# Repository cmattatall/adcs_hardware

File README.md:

# adcs_hardware
Hardware repository for ADCS

# Harware Architecture Overview

# VERSION CONTROL

WHENEVER A SHEMATIC REVISION IS COMPLETED, UNLIKE SOFTWARE, BRANCHES SHOULD NOT BE MERGED. THEY SHOULD BE FROZEN.

TO START A REVISION, THE CURRENT "HEAD" SHOULD BE FORKED (READ: MAKE A NEW BRANCH) NAMED APPROPRIATELY. 

If the revision is accepted and the design changes pass review, the revision branch then becomes the new master branch.

This way, the last "stable" revision branch (the old master branch) remains completely unchanged and unaffected by deltas made in the forked branch.

If there is ever an issue, the old version can be selected SIMPLY by switching back to the old branch, no merging should ever occur.

# Cloning repo for use in Eagle

Clone Repo into your local eagle projects repository
ie: C:/Users/user/Documents/Eagle/projects/

Repo will then appear under projects tab of the 'Control Panel' window when Eagle is launched.

# Eagle File Types Notes
 
## Project Manager File
*.epf is the eagle project manager file and contains all settings information for project. Contains all path references to all the libraries the have been used. *.epf is not crucial to project but can be useful to share with collaborators. 

## Design Files 
*.brd and *.sch files must have matching names and be contained in the same folder. Schematic files also copy all the information from the component libraries once the components are placed in a schematic, making the library files less necessary once used. The .brd files also copy the package information from the component libraries and don’t require libraries again unless you need to place a new component or replace a previous component. 

## Backup Files
*.b#x and *.s#x files are local backups by Eagle. By default Eagle saves 9 backups (9 is also the max).

## Libraries
Libraries are the templates for components. They are unique files that all the information on a specific component that Eagle CAD requires for design. They are the building blocks that contain information like pin numbers, terminal names, symbol shape, package type and footprint size etc. A library has both a symbol (used in schematics) and a package (footprint for pcb layout). Once a library is used in an Eagle design, it is no longer required as Eagle copies all the information over to the schematic and board files. However, while working with your team, it is recommended to share and use the same libraries to keep your designs consistent.

Custom library parts have been saved in managed library: https://library.io/libraries/22876504-my_library

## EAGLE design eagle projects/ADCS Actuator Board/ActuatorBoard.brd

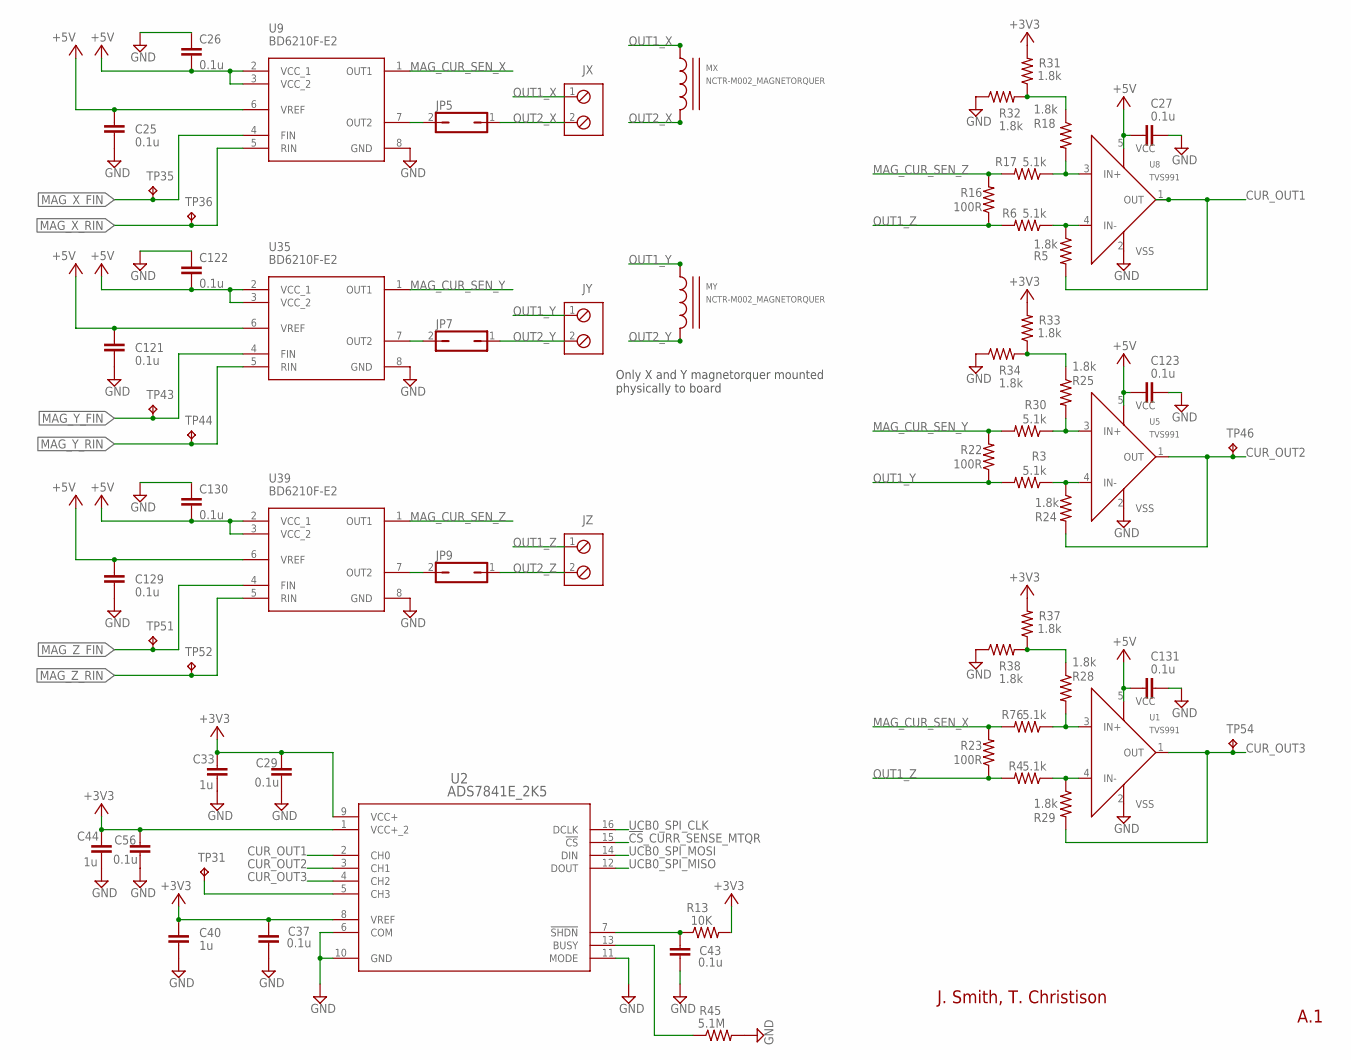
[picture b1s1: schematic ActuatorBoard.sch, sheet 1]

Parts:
C25, C26, C121, C122, C129, C130: 0.1u; C0603
C27, C29, C37, C43, C56, C123, C131: 0.1u; C0402
C33, C40, C44: 1u; C0402
JP5, JP7, JP9: JP1Q_; 1X02
JX: TRM_BLK_1X2; 2POL254
JY: TRM_BLK_1X2; 2POL254
JZ: TRM_BLK_1X2; 2POL254
MX: NCTR-M002_MAGNETORQUER; MAG_MOUNT_V3
MY: NCTR-M002_MAGNETORQUER; MAG_MOUNT_V3
R3, R4, R6, R17, R30, R76: 5.1k; R0402
R5, R18, R24, R25, R28, R29, R31, R32, R33, R34, R37, R38: 1.8k; R0402
R13: 10K; R0402
R16, R22, R23: 100R; M0805
R45: 5.1M; R0402
TP31, TP35, TP36, TP43, TP44, TP46, TP51, TP52, TP54: TESTPOINT; TP_P76H50
U1, U5, U8: TVS991; SOT95P280X145-5N
U2: ADS7841E_2K5; DBQ16
U9, U35, U39: BD6210F-E2; BD6221F-E2_SOIC8P127_500X620X171L30X42N

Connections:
!CS!_CURR_SENSE_MTQR: U2.15 (!CS); also elsewhere on the board
+3V3: C29.1, C33.1, C37.1, C40.1, C44.1, C56.1, R13.2, R31.2, R33.2, R37.2, U2.1 (VCC+_2), U2.8 (VREF), U2.9 (VCC+); also elsewhere on the board
+5V: C25.1, C26.2, C27.1, C121.1, C122.2, C123.1, C129.1, C130.2, C131.1, U1.5 (VCC), U5.5 (VCC), U8.5 (VCC), U9.2 (VCC_1), U9.3 (VCC_2), U9.6 (VREF), U35.2 (VCC_1), U35.3 (VCC_2), U35.6 (VREF), U39.2 (VCC_1), U39.3 (VCC_2), U39.6 (VREF); also elsewhere on the board
CUR_OUT1: R5.2, U2.2 (CH0), U8.1 (OUT)
CUR_OUT2: R24.2, TP46.1, U2.3 (CH1), U5.1 (OUT)
CUR_OUT3: R29.2, TP54.1, U1.1 (OUT), U2.4 (CH2)
GND: C25.2, C26.1, C27.2, C29.2, C33.2, C37.2, C40.2, C43.2, C44.2, C56.2, C121.2, C122.1, C123.2, C129.2, C130.1, C131.2, R32.1, R34.1, R38.1, R45.2, U1.2 (VSS), U2.6 (COM), U2.10 (GND), U2.11 (MODE), U5.2 (VSS), U8.2 (VSS), U9.8 (GND), U35.8 (GND), U39.8 (GND); also elsewhere on the board
MAG_CUR_SEN_X: R23.2, R76.2, U9.1 (OUT1)
MAG_CUR_SEN_Y: R22.2, R30.2, U35.1 (OUT1)
MAG_CUR_SEN_Z: R16.2, R17.2, U39.1 (OUT1)
MAG_X_FIN: TP35.1, U9.4 (FIN); also elsewhere on the board
MAG_X_RIN: TP36.1, U9.5 (RIN); also elsewhere on the board
MAG_Y_FIN: TP43.1, U35.4 (FIN)
MAG_Y_RIN: TP44.1, U35.5 (RIN); also elsewhere on the board
MAG_Z_FIN: TP51.1, U39.4 (FIN); also elsewhere on the board
MAG_Z_RIN: TP52.1, U39.5 (RIN); also elsewhere on the board
unnamed: R45.1, U2.13 (BUSY)
unnamed: R5.1, R6.1, U8.4 (IN-)
unnamed: R3.1, R24.1, U5.4 (IN-)
unnamed: R4.1, R29.1, U1.4 (IN-)
unnamed: R17.1, R18.2, U8.3 (IN+)
unnamed: R25.2, R30.1, U5.3 (IN+)
unnamed: R28.2, R76.1, U1.3 (IN+)
unnamed: C43.1, R13.1, U2.7 (!SHDN)
unnamed: TP31.1, U2.5 (CH3)
unnamed: JP5.2, U9.7 (OUT2)
unnamed: R33.1, R34.2
unnamed: R28.1, R37.1, R38.2
unnamed: R18.1, R31.1, R32.2
unnamed: JP7.2, U35.7 (OUT2)
unnamed: JP9.2, U39.7 (OUT2)
OUT1_X: JX.1
OUT1_Y: JY.1, R3.2, R22.1
OUT1_Z: JZ.1, R4.2, R6.2, R16.1, R23.1
OUT2_X: JP5.1, JX.2
OUT2_Y: JP7.1, JY.2
OUT2_Z: JP9.1, JZ.2
UCB0_SPI_CLK: U2.16 (DCLK); also elsewhere on the board
UCB0_SPI_MISO: U2.12 (DOUT); also elsewhere on the board
UCB0_SPI_MOSI: U2.14 (DIN); also elsewhere on the board

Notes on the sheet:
A.1
Only X and Y magnetorquer mounted physically to board
J. Smith, T. Christison

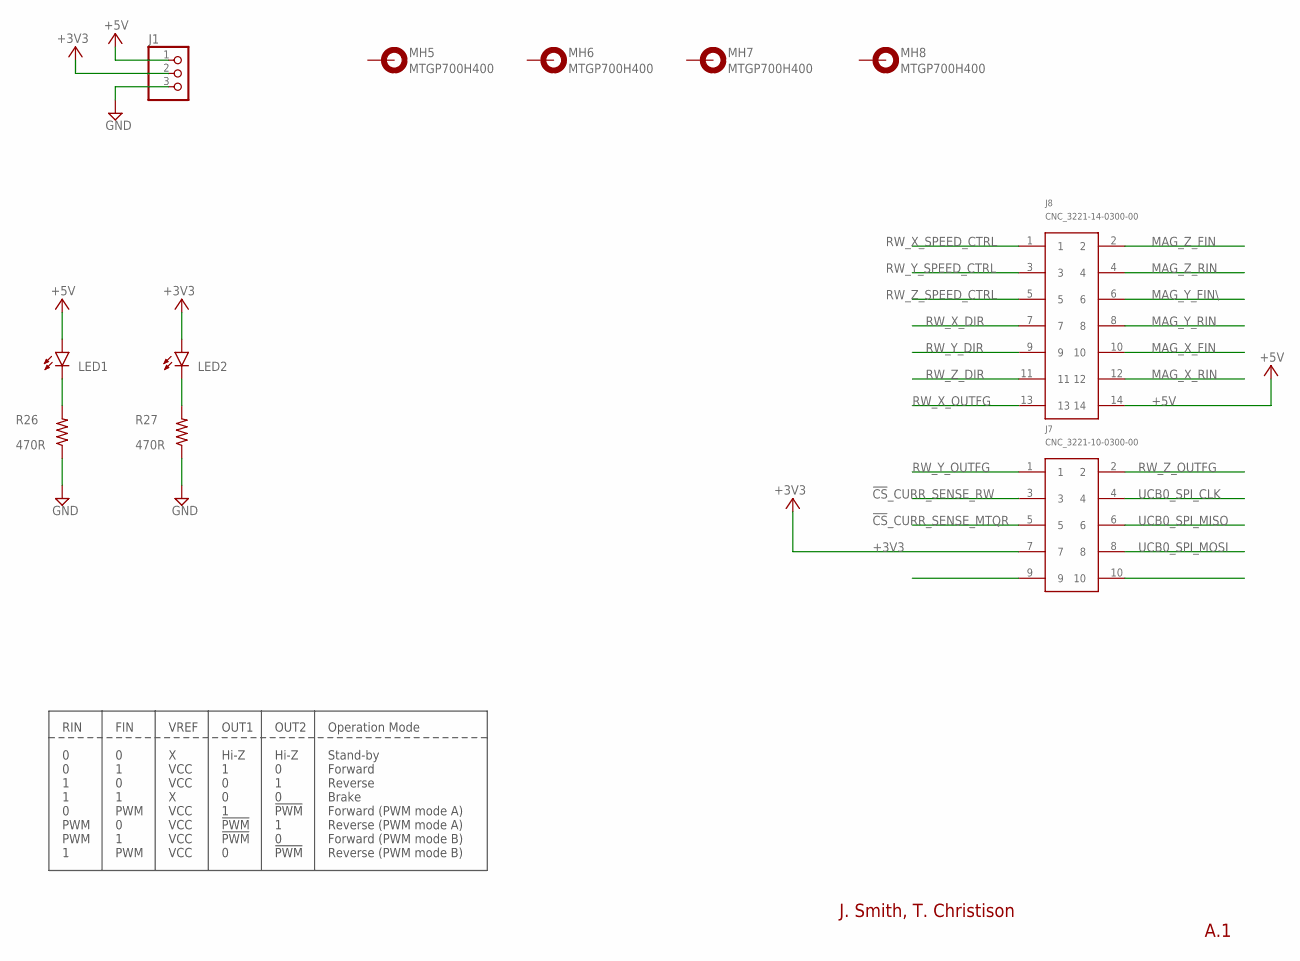
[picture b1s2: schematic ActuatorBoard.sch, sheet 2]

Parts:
J1: PINHD-1X3; 1X03
J7: CNC_3221-10-0300-00
J8: CNC_3221-14-0300-00
LED1, LED2: LEDCHIPLED_0603; CHIPLED_0603
MH5, MH6, MH7, MH8: MTGP700H400
R26, R27: 470R; R0603

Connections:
!CS!_CURR_SENSE_MTQR: J7.5; also elsewhere on the board
!CS!_CURR_SENSE_RW: J7.3; also elsewhere on the board
+3V3: J1.2, J7.7, LED2.A; also elsewhere on the board
+5V: J1.1, J8.14, LED1.A; also elsewhere on the board
GND: J1.3, R26.1, R27.1; also elsewhere on the board
MAG_X_FIN: J8.10; also elsewhere on the board
MAG_X_RIN: J8.12; also elsewhere on the board
MAG_Y_FIN\: J8.6
MAG_Y_RIN: J8.8; also elsewhere on the board
MAG_Z_FIN: J8.2; also elsewhere on the board
MAG_Z_RIN: J8.4; also elsewhere on the board
unnamed: LED1.C, R26.2
unnamed: LED2.C, R27.2
RW_X_DIR: J8.7; also elsewhere on the board
RW_X_OUTFG: J8.13; also elsewhere on the board
RW_X_SPEED_CTRL: J8.1; also elsewhere on the board
RW_Y_DIR: J8.9; also elsewhere on the board
RW_Y_OUTFG: J7.1; also elsewhere on the board
RW_Y_SPEED_CTRL: J8.3; also elsewhere on the board
RW_Z_DIR: J8.11; also elsewhere on the board
RW_Z_OUTFG: J7.2; also elsewhere on the board
RW_Z_SPEED_CTRL: J8.5; also elsewhere on the board
UCB0_SPI_CLK: J7.4; also elsewhere on the board
UCB0_SPI_MISO: J7.6; also elsewhere on the board
UCB0_SPI_MOSI: J7.8; also elsewhere on the board

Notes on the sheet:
A.1
FIN 0 1 0 1 PWM 0 1 PWM
RIN 0 0 1 1 0 PWM PWM 1
VREF X VCC VCC X VCC VCC VCC VCC
OUT1 Hi-Z 1 0 0 1 !PWM !PWM 0
OUT2 Hi-Z 0 1 0 !PWM 1 0 !PWM
Operation Mode Stand-by Forward Reverse Brake Forward (PWM mode A) Reverse (PWM mode A) Forward (PWM mode B) Reverse (PWM mode B)
J. Smith, T. Christison

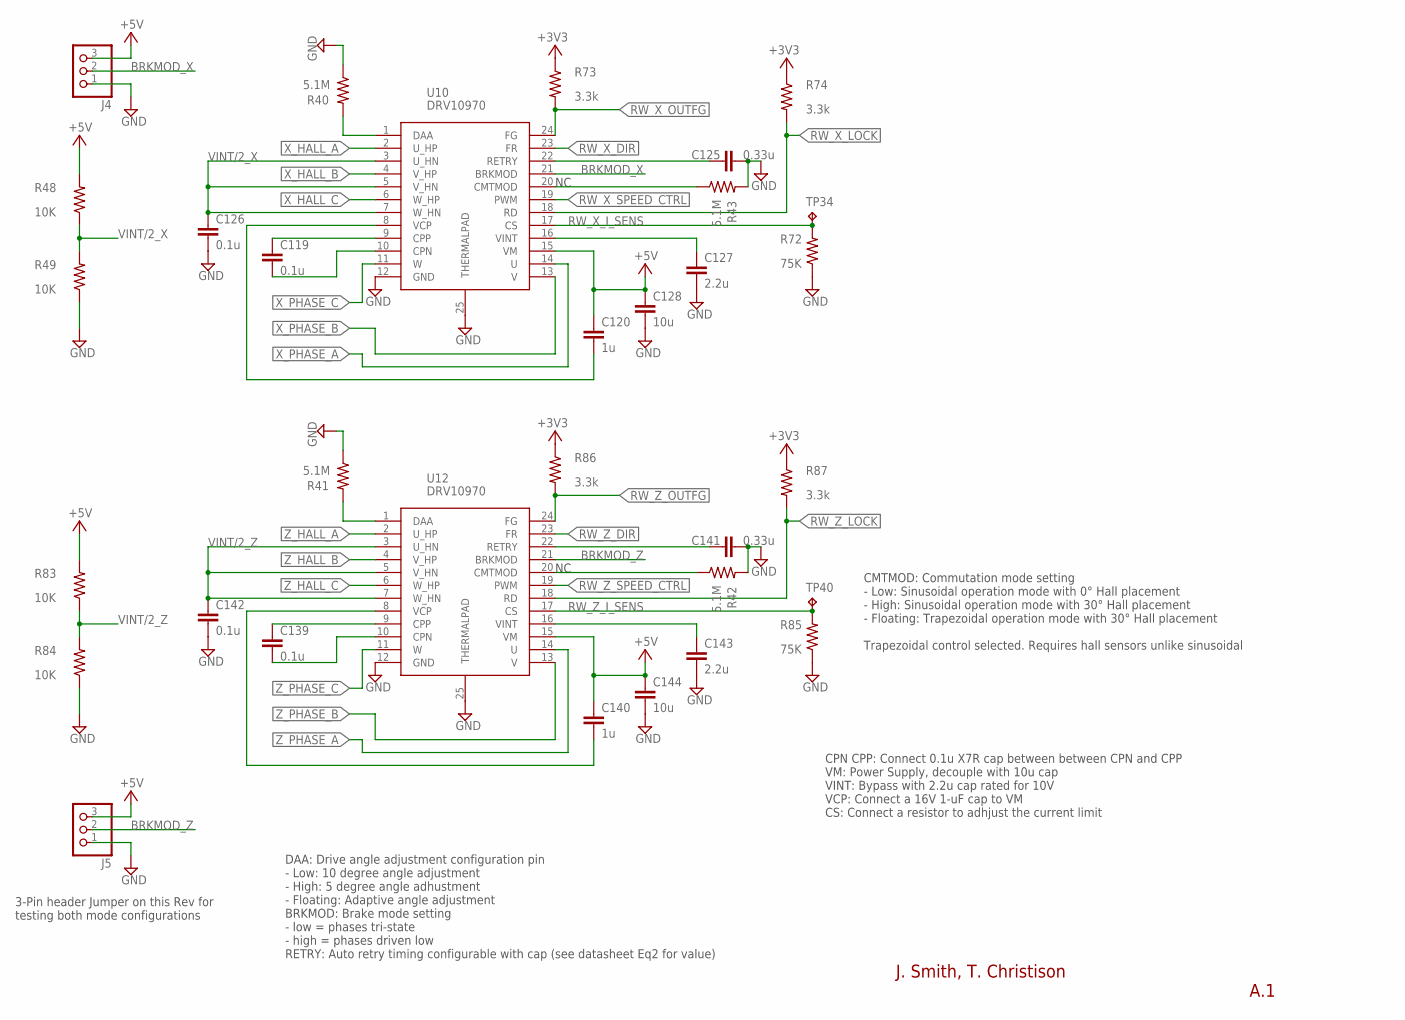
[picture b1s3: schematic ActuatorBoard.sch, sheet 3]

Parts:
C119, C126, C139, C142: 0.1u; C0603
C120, C140: 1u; C0603
C125, C141: 0.33u; C0603
C127, C143: 2.2u; C0603
C128, C144: 10u; C0603
J4, J5: PINHD-1X3; 1X03
R40, R41, R42, R43: 5.1M; R0402
R48, R49, R83, R84: 10K; R0603
R72, R85: 75K; R0603
R73, R74, R86, R87: 3.3k; R0603
TP34, TP40: TESTPOINT; TP_P76H50
U10, U12: DRV10970_MOTOR_DRIVERDRV10970; SOP65P640X120-25T240X328N

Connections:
+3V3: R73.1, R74.1, R86.1, R87.1; also elsewhere on the board
+5V: C120.1, C128.1, C140.1, C144.1, J4.3, J5.3, R48.2, R83.2, U10.15 (VM), U12.15 (VM); also elsewhere on the board
BRKMOD_X: J4.2, U10.21 (BRKMOD)
BRKMOD_Z: J5.2, U12.21 (BRKMOD)
GND: C125.2, C126.2, C127.2, C128.2, C141.2, C142.2, C143.2, C144.2, J4.1, J5.1, R40.1, R41.1, R42.2, R43.2, R49.1, R72.1, R84.1, R85.1, U10.12 (GND), U10.25 (THERMALPAD), U12.12 (GND), U12.25 (THERMALPAD); also elsewhere on the board
unnamed: R40.2, U10.1 (DAA)
unnamed: R41.2, U12.1 (DAA)
unnamed: R42.1, U12.20 (CMTMOD)
unnamed: R43.1, U10.20 (CMTMOD)
unnamed: C119.1, U10.9 (CPP)
unnamed: C120.2, U10.8 (VCP)
unnamed: C119.2, U10.10 (CPN)
unnamed: C127.1, U10.16 (VINT)
unnamed: C125.1, U10.22 (RETRY)
unnamed: C139.1, U12.9 (CPP)
unnamed: C140.2, U12.8 (VCP)
unnamed: C139.2, U12.10 (CPN)
unnamed: C143.1, U12.16 (VINT)
unnamed: C141.1, U12.22 (RETRY)
RW_X_DIR: U10.23 (FR); also elsewhere on the board
RW_X_I_SENS: R72.2, TP34.1, U10.17 (CS); also elsewhere on the board
RW_X_LOCK: R74.2, U10.18 (RD)
RW_X_OUTFG: R73.2, U10.24 (FG); also elsewhere on the board
RW_X_SPEED_CTRL: U10.19 (PWM); also elsewhere on the board
RW_Z_DIR: U12.23 (FR); also elsewhere on the board
RW_Z_I_SENS: R85.2, TP40.1, U12.17 (CS); also elsewhere on the board
RW_Z_LOCK: R87.2, U12.18 (RD)
RW_Z_OUTFG: R86.2, U12.24 (FG); also elsewhere on the board
RW_Z_SPEED_CTRL: U12.19 (PWM); also elsewhere on the board
VINT/2_X: C126.1, R48.1, R49.2, U10.3 (U_HN), U10.5 (V_HN), U10.7 (W_HN)
VINT/2_Z: C142.1, R83.1, R84.2, U12.3 (U_HN), U12.5 (V_HN), U12.7 (W_HN)
X_HALL_A: U10.2 (U_HP); also elsewhere on the board
X_HALL_B: U10.4 (V_HP); also elsewhere on the board
X_HALL_C: U10.6 (W_HP); also elsewhere on the board
X_PHASE_A: U10.14 (U); also elsewhere on the board
X_PHASE_B: U10.13 (V); also elsewhere on the board
X_PHASE_C: U10.11 (W); also elsewhere on the board
Z_HALL_A: U12.2 (U_HP); also elsewhere on the board
Z_HALL_B: U12.4 (V_HP); also elsewhere on the board
Z_HALL_C: U12.6 (W_HP); also elsewhere on the board
Z_PHASE_A: U12.14 (U); also elsewhere on the board
Z_PHASE_B: U12.13 (V); also elsewhere on the board
Z_PHASE_C: U12.11 (W); also elsewhere on the board

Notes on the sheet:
CPN CPP: Connect 0.1u X7R cap between between CPN and CPP VM: Power Supply, decouple with 10u cap VINT: Bypass with 2.2u cap rated for 10V VCP: Connect a 16V 1-uF cap to VM CS: Connect a resistor to adhjust the current limit
DAA: Drive angle adjustment configuration pin - Low: 10 degree angle adjustment - High: 5 degree angle adhustment - Floating: Adaptive angle adjustment BRKMOD: Brake mode setting - low = phases tri-state - high = phases driven low RETRY: Auto retry timing configurable with cap (see datasheet Eq2 fo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
CMTMOD: Commutation mode setting - Low: Sinusoidal operation mode with 0° Hall placement - High: Sinusoidal operation mode with 30° Hall placement - Floating: Trapezoidal operation mode with 30° Hall placement Trapezoidal control selected. Requires hall sensors unlike sinusoidal
A.1
3-Pin header Jumper on this Rev for testing both mode configurations
J. Smith, T. Christison

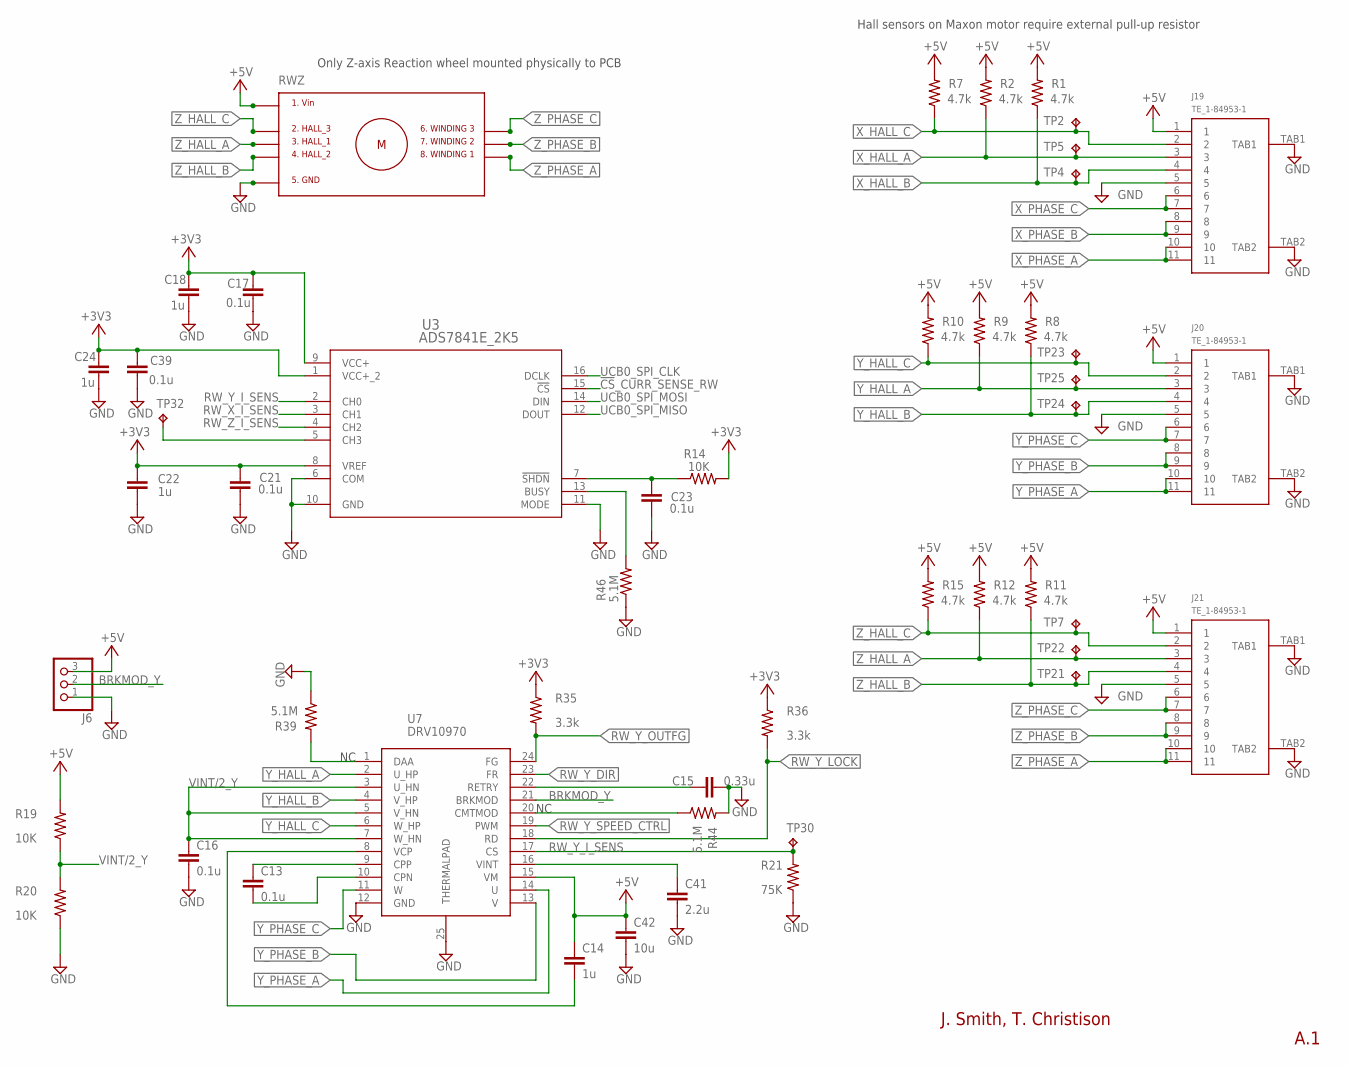
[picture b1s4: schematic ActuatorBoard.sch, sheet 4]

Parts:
C13, C16: 0.1u; C0603
C14: 1u; C0603
C15: 0.33u; C0603
C17, C21, C23, C39: 0.1u; C0402
C18, C22, C24: 1u; C0402
C41: 2.2u; C0603
C42: 10u; C0603
J6: PINHD-1X3; 1X03
J19, J20, J21: TE_1-84953-1
R1, R2, R7, R8, R9, R10, R11, R12, R15: 4.7k; R0402
R14: 10K; R0402
R19, R20: 10K; R0603
R21: 75K; R0603
R35, R36: 3.3k; R0603
R39, R44, R46: 5.1M; R0402
RWZ: REACTION_WHEEL_NOPINS_MAXON; RWA_NOPINS
TP2, TP4, TP5, TP7, TP21, TP22, TP23, TP24, TP25, TP30, TP32: TESTPOINT; TP_P76H50
U3: ADS7841E_2K5; DBQ16
U7: DRV10970_MOTOR_DRIVERDRV10970; SOP65P640X120-25T240X328N

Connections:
!CS!_CURR_SENSE_RW: U3.15 (!CS); also elsewhere on the board
+3V3: C17.1, C18.1, C21.1, C22.1, C24.1, C39.1, R14.2, R35.1, R36.1, U3.1 (VCC+_2), U3.8 (VREF), U3.9 (VCC+); also elsewhere on the board
+5V: C14.1, C42.1, J6.3, J19.1, J20.1, J21.1, R1.2, R2.2, R7.2, R8.2, R9.2, R10.2, R11.2, R12.2, R15.2, R19.2, U7.15 (VM); also elsewhere on the board
BRKMOD_Y: J6.2, U7.21 (BRKMOD)
GND: C15.2, C16.2, C17.2, C18.2, C21.2, C22.2, C23.2, C24.2, C39.2, C41.2, C42.2, J6.1, J19.5, J19.TAB1, J19.TAB2, J20.5, J20.TAB1, J20.TAB2, J21.5, J21.TAB1, J21.TAB2, R20.1, R21.1, R39.1, R44.2, R46.1, U3.6 (COM), U3.10 (GND), U3.11 (MODE), U7.12 (GND), U7.25 (THERMALPAD); also elsewhere on the board
unnamed: R46.2, U3.13 (BUSY)
unnamed: R39.2, U7.1 (DAA)
unnamed: C23.1, R14.1, U3.7 (!SHDN)
unnamed: TP32.1, U3.5 (CH3)
unnamed: R44.1, U7.20 (CMTMOD)
unnamed: C13.1, U7.9 (CPP)
unnamed: C14.2, U7.8 (VCP)
unnamed: C13.2, U7.10 (CPN)
unnamed: C41.1, U7.16 (VINT)
unnamed: C15.1, U7.22 (RETRY)
RW_X_I_SENS: U3.3 (CH1); also elsewhere on the board
RW_Y_DIR: U7.23 (FR); also elsewhere on the board
RW_Y_I_SENS: R21.2, TP30.1, U3.2 (CH0), U7.17 (CS)
RW_Y_LOCK: R36.2, U7.18 (RD)
RW_Y_OUTFG: R35.2, U7.24 (FG); also elsewhere on the board
RW_Y_SPEED_CTRL: U7.19 (PWM); also elsewhere on the board
RW_Z_I_SENS: U3.4 (CH2); also elsewhere on the board
UCB0_SPI_CLK: U3.16 (DCLK); also elsewhere on the board
UCB0_SPI_MISO: U3.12 (DOUT); also elsewhere on the board
UCB0_SPI_MOSI: U3.14 (DIN); also elsewhere on the board
VINT/2_Y: C16.1, R19.1, R20.2, U7.3 (U_HN), U7.5 (V_HN), U7.7 (W_HN)
X_HALL_A: J19.3, R2.1, TP5.1; also elsewhere on the board
X_HALL_B: J19.4, R1.1, TP4.1; also elsewhere on the board
X_HALL_C: J19.2, R7.1, TP2.1; also elsewhere on the board
X_PHASE_A: J19.10, J19.11; also elsewhere on the board
X_PHASE_B: J19.8, J19.9; also elsewhere on the board
X_PHASE_C: J19.6, J19.7; also elsewhere on the board
Y_HALL_A: J20.3, R9.1, TP25.1, U7.2 (U_HP)
Y_HALL_B: J20.4, R8.1, TP24.1, U7.4 (V_HP)
Y_HALL_C: J20.2, R10.1, TP23.1, U7.6 (W_HP)
Y_PHASE_A: J20.10, J20.11, U7.14 (U)
Y_PHASE_B: J20.8, J20.9, U7.13 (V)
Y_PHASE_C: J20.6, J20.7, U7.11 (W)
Z_HALL_A: J21.3, R12.1, TP22.1; also elsewhere on the board
Z_HALL_B: J21.4, R11.1, TP21.1; also elsewhere on the board
Z_HALL_C: J21.2, R15.1, TP7.1; also elsewhere on the board
Z_PHASE_A: J21.10, J21.11; also elsewhere on the board
Z_PHASE_B: J21.8, J21.9; also elsewhere on the board
Z_PHASE_C: J21.6, J21.7; also elsewhere on the board

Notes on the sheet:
A.1
Hall sensors on Maxon motor require external pull-up resistor
Only Z-axis Reaction wheel mounted physically to PCB
J. Smith, T. Christison

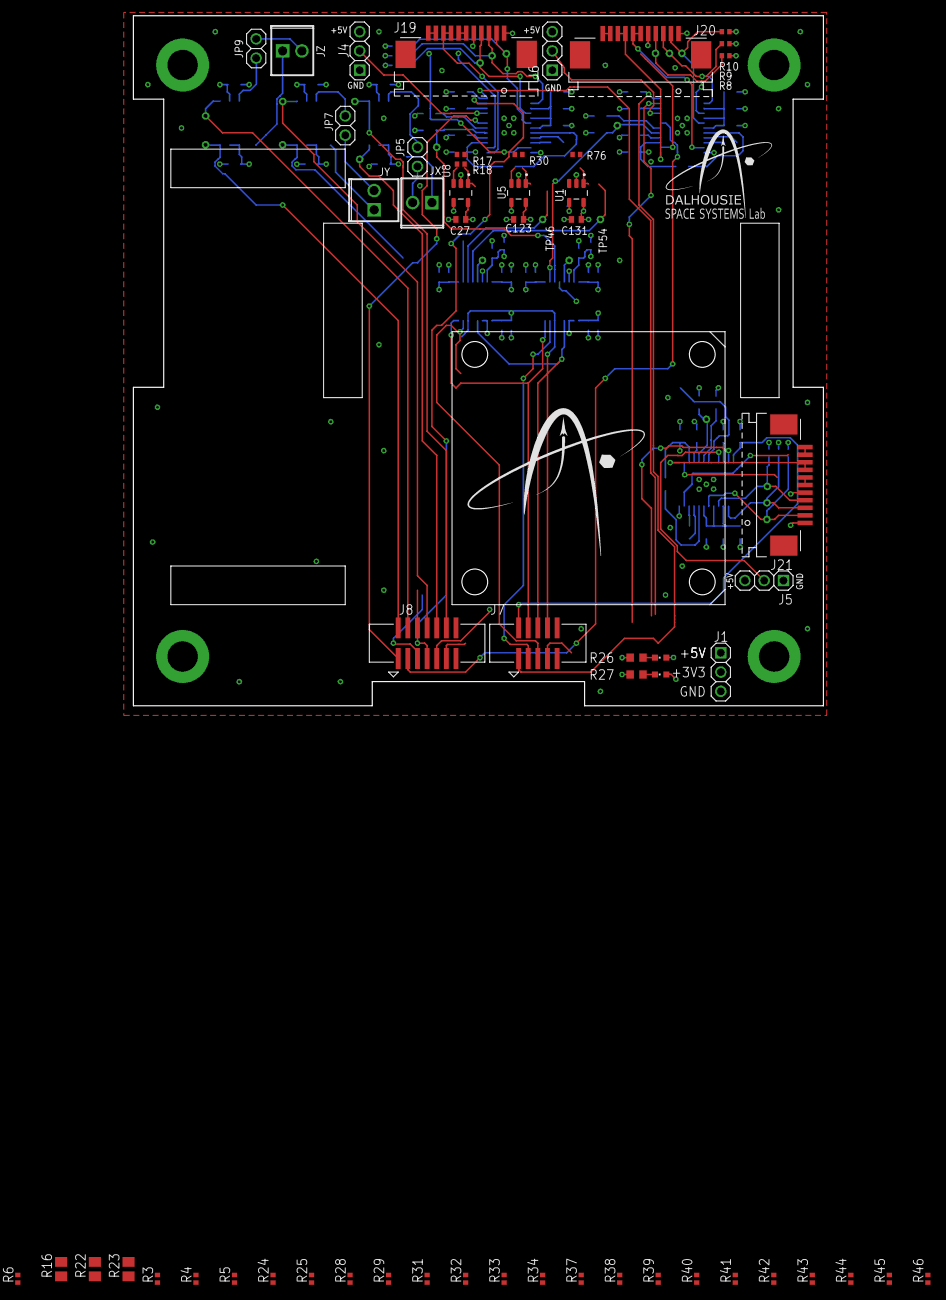
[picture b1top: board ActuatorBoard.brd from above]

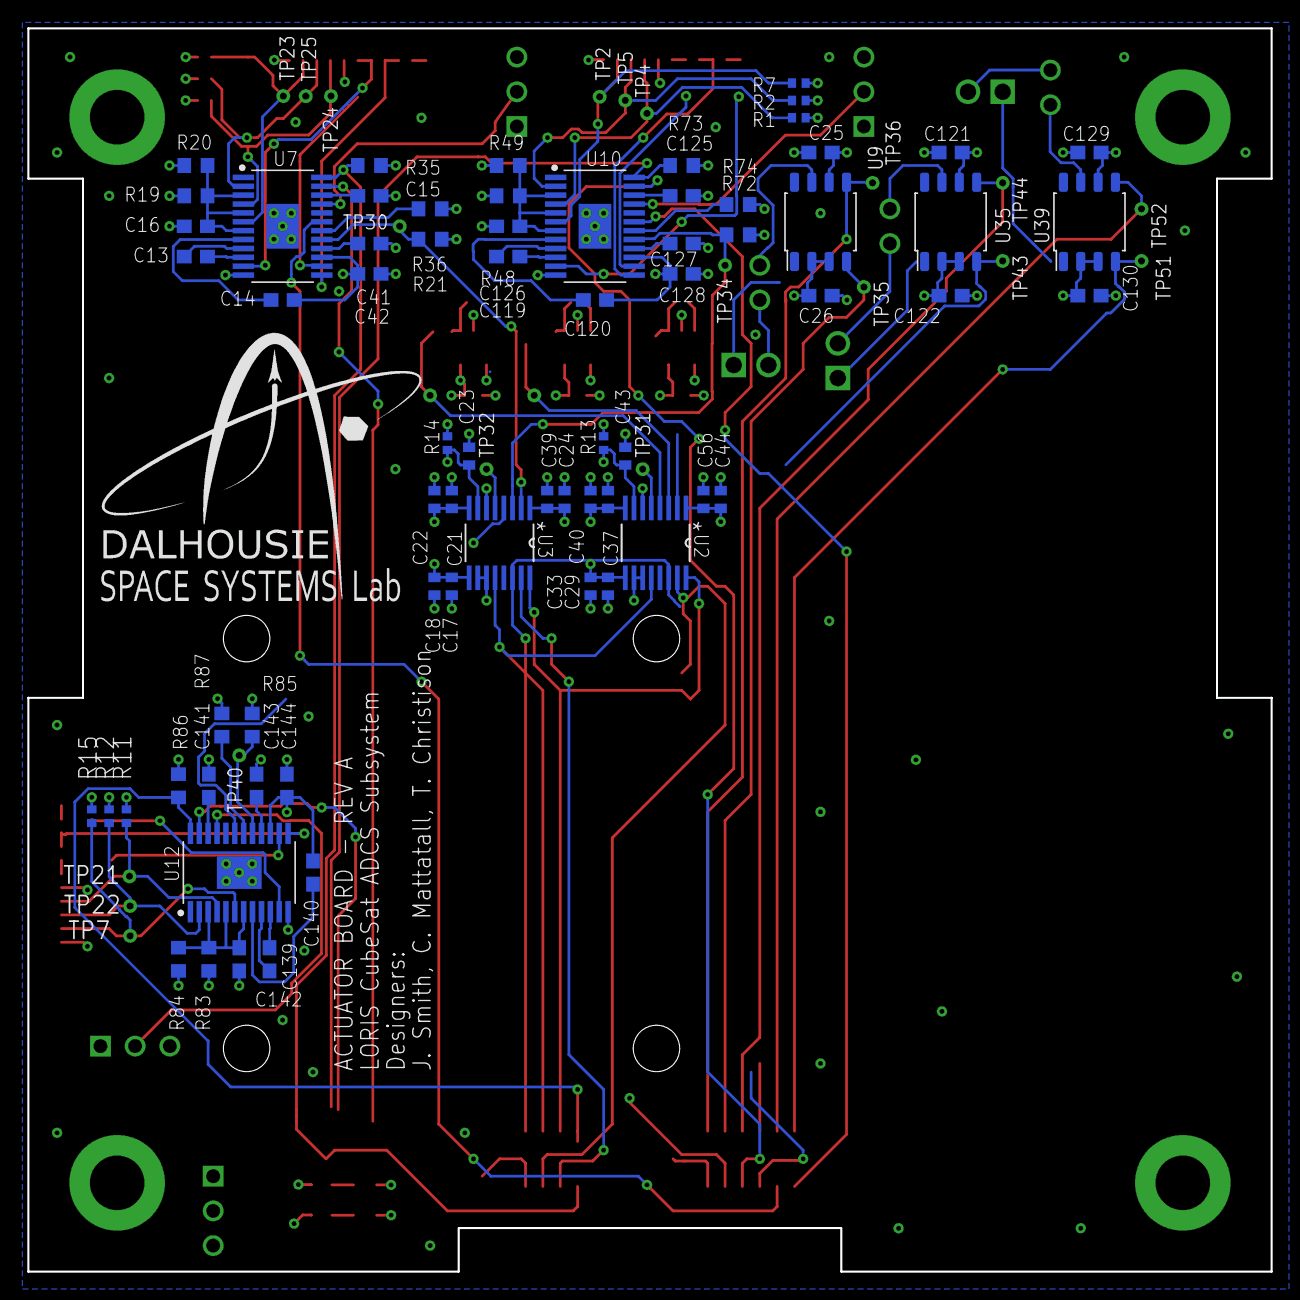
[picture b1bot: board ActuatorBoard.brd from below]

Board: 4 copper layers, 91.0 x 91.0 mm, 155 parts (89 on the bottom side), 105 nets.

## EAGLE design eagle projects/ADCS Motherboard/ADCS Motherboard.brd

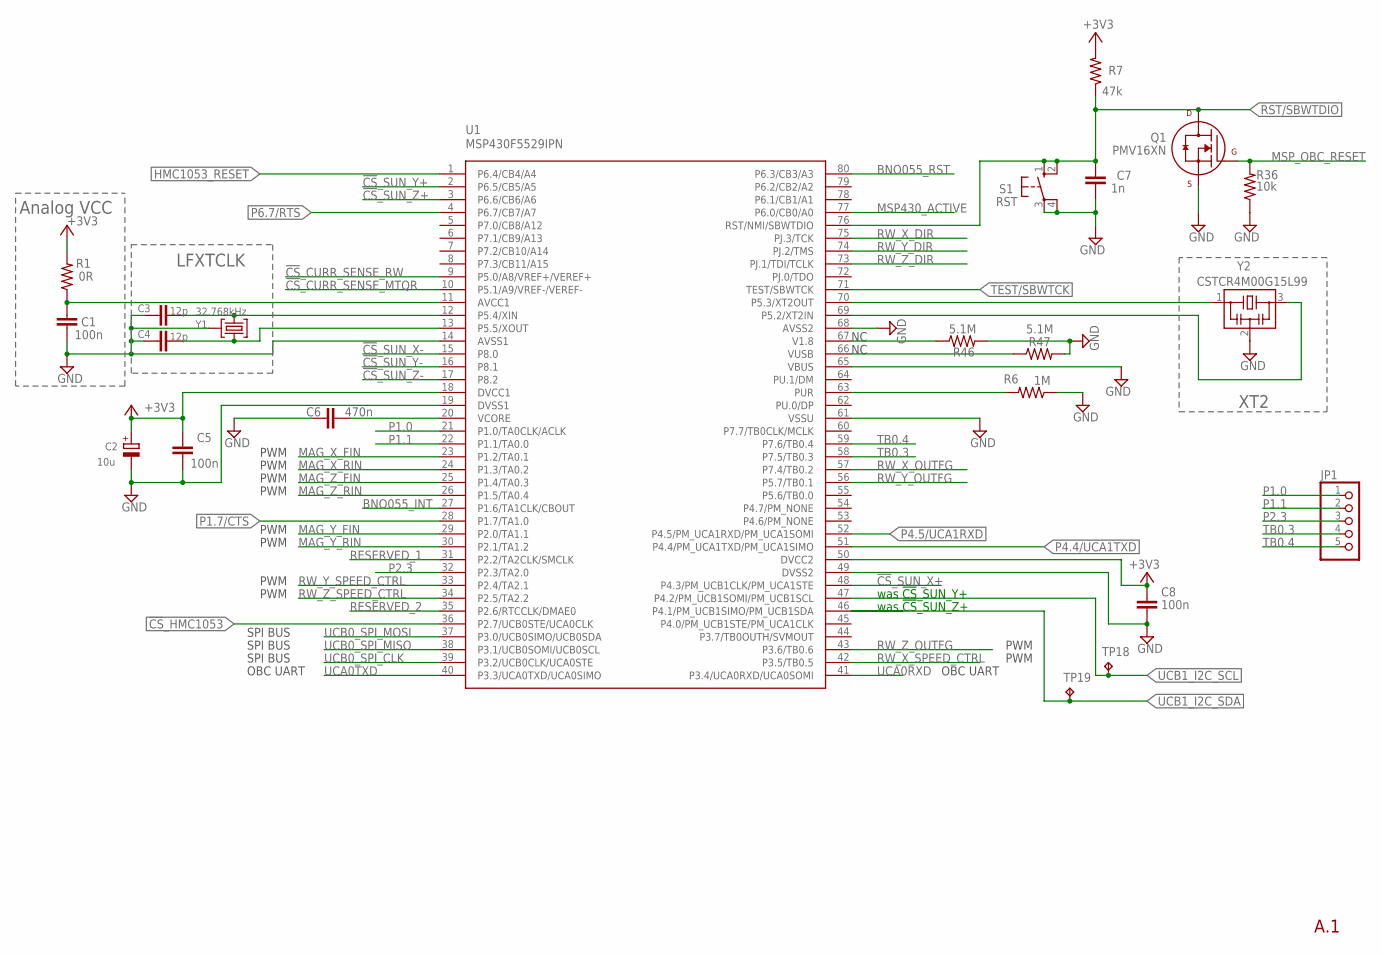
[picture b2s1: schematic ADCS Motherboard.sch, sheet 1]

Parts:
C1, C5, C8: 100n; C0402
C2: 10u; A/3216-18R
C3, C4: 12p; C0402
C6: 470n; C0402
C7: 1n; C0402
JP1: PINHD-1X5; 1X05
Q1: PMV16XN; SOT23-3P95_230X110L20X43N_PMV16XN
R1: 0R; R0402
R6: 1M; R0603
R7: 47k; R0402
R36: 10k; R0603
R46, R47: 5.1M; R0402
S1: RST; B3F-10XX
TP18, TP19: TESTPOINT; TP_P76H50
U1: MSP430F5529IPN; QFP80P50_1400X1400X160L60X22N
Y1: 32.768kHz; MS3V-T1R
Y2: CSTCR4M00G15L99; MURATA-FILTER_CSTCR

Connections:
!CS!_CURR_SENSE_MTQR: U1.10 (P5.1/A9/VREF-/VEREF-); also elsewhere on the board
!CS!_CURR_SENSE_RW: U1.9 (P5.0/A8/VREF+/VEREF+); also elsewhere on the board
!CS!_HMC1053: U1.36 (P2.7/UCB0STE/UCA0CLK); also elsewhere on the board
!CS!_SUN_X+: U1.48 (P4.3/PM_UCB1CLK/PM_UCA1STE); also elsewhere on the board
!CS!_SUN_X-: U1.15 (P8.0); also elsewhere on the board
!CS!_SUN_Y+: U1.2 (P6.5/CB5/A5); also elsewhere on the board
!CS!_SUN_Y-: U1.16 (P8.1); also elsewhere on the board
!CS!_SUN_Z+: U1.3 (P6.6/CB6/A6); also elsewhere on the board
!CS!_SUN_Z-: U1.17 (P8.2); also elsewhere on the board
+3V3: C2.+, C5.2, C8.1, R1.2, R7.2, U1.18 (DVCC1), U1.50 (DVCC2); also elsewhere on the board
AVCC1: C1.1, R1.1, U1.11 (AVCC1)
BNO055_INT: U1.27 (P1.6/TA1CLK/CBOUT); also elsewhere on the board
BNO055_RST: U1.80 (P6.3/CB3/A3); also elsewhere on the board
GND: C1.2, C2.-, C3.1, C4.1, C5.1, C6.1, C7.2, C8.2, Q1.2 (S), R6.1, R36.1, R46.2, R47.2, S1.3, S1.4 (P1), U1.14 (AVSS1), U1.19 (DVSS1), U1.49 (DVSS2), U1.61 (VSSU), U1.65 (VBUS), U1.68 (AVSS2), Y1.P3 (GND), Y2.2; also elsewhere on the board
HMC1053_RESET: U1.1 (P6.4/CB4/A4); also elsewhere on the board
MAG_X_FIN: U1.23 (P1.2/TA0.1); also elsewhere on the board
MAG_X_RIN: U1.24 (P1.3/TA0.2); also elsewhere on the board
MAG_Y_FIN: U1.29 (P2.0/TA1.1); also elsewhere on the board
MAG_Y_RIN: U1.30 (P2.1/TA1.2); also elsewhere on the board
MAG_Z_FIN: U1.25 (P1.4/TA0.3); also elsewhere on the board
MAG_Z_RIN: U1.26 (P1.5/TA0.4); also elsewhere on the board
MSP430_ACTIVE: U1.77 (P6.0/CB0/A0); also elsewhere on the board
MSP_OBC_RESET: Q1.1 (G), R36.2; also elsewhere on the board
unnamed: R46.1, U1.67 (V1.8)
unnamed: R47.1, U1.66 (VUSB)
P1.0: JP1.1, U1.21 (P1.0/TA0CLK/ACLK)
P1.1: JP1.2, U1.22 (P1.1/TA0.0)
P1.7/CTS: U1.28 (P1.7/TA1.0); also elsewhere on the board
P2.3: JP1.3, U1.32 (P2.3/TA2.0)
P4.4/UCA1TXD: U1.51 (P4.4/PM_UCA1TXD/PM_UCA1SIMO); also elsewhere on the board
P4.5/UCA1RXD: U1.52 (P4.5/PM_UCA1RXD/PM_UCA1SOMI); also elsewhere on the board
P5.2/XT2IN1: U1.69 (P5.2/XT2IN), Y2.3
P5.3/XT2OUT1: U1.70 (P5.3/XT2OUT), Y2.1
P5.4/XIN1: C3.2, U1.12 (P5.4/XIN), Y1.P2 (2)
P5.5/XOUT1: C4.2, U1.13 (P5.5/XOUT), Y1.P1 (1)
P6.7/RTS: U1.4 (P6.7/CB7/A7); also elsewhere on the board
RESERVED_1: U1.31 (P2.2/TA2CLK/SMCLK); also elsewhere on the board
RESERVED_2: U1.35 (P2.6/RTCCLK/DMAE0); also elsewhere on the board
RST/SBWTDIO: C7.1, Q1.3 (D), R7.1, S1.1 (S), S1.2 (S1), U1.76 (RST/NMI/SBWTDIO); also elsewhere on the board
RW_X_DIR: U1.75 (PJ.3/TCK); also elsewhere on the board
RW_X_OUTFG: U1.57 (P7.4/TB0.2); also elsewhere on the board
RW_X_SPEED_CTRL: U1.42 (P3.5/TB0.5); also elsewhere on the board
RW_Y_DIR: U1.74 (PJ.2/TMS); also elsewhere on the board
RW_Y_OUTFG: U1.56 (P5.7/TB0.1); also elsewhere on the board
RW_Y_SPEED_CTRL: U1.33 (P2.4/TA2.1); also elsewhere on the board
RW_Z_DIR: U1.73 (PJ.1/TDI/TCLK); also elsewhere on the board
RW_Z_OUTFG: U1.43 (P3.6/TB0.6); also elsewhere on the board
RW_Z_SPEED_CTRL: U1.34 (P2.5/TA2.2); also elsewhere on the board
TARGET_PUR: R6.2, U1.63 (PUR)
TB0.3: JP1.4, U1.58 (P7.5/TB0.3)
TB0.4: JP1.5, U1.59 (P7.6/TB0.4)
TEST/SBWTCK: U1.71 (TEST/SBWTCK); also elsewhere on the board
UCA0RXD: U1.41 (P3.4/UCA0RXD/UCA0SOMI); also elsewhere on the board
UCA0TXD: U1.40 (P3.3/UCA0TXD/UCA0SIMO); also elsewhere on the board
UCB0_SPI_CLK: U1.39 (P3.2/UCB0CLK/UCA0STE); also elsewhere on the board
UCB0_SPI_MISO: U1.38 (P3.1/UCB0SOMI/UCB0SCL); also elsewhere on the board
UCB0_SPI_MOSI: U1.37 (P3.0/UCB0SIMO/UCB0SDA); also elsewhere on the board
UCB1_I2C_SCL: TP18.1, U1.47 (P4.2/PM_UCB1SOMI/PM_UCB1SCL); also elsewhere on the board
UCB1_I2C_SDA: TP19.1, U1.46 (P4.1/PM_UCB1SIMO/PM_UCB1SDA); also elsewhere on the board
VCORE1: C6.2, U1.20 (VCORE)

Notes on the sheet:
LFXTCLK
XT2
Analog VCC
PWM
OBC UART
SPI BUS
was !CS!_SUN_Y+
was !CS!_SUN_Z+
A.1
